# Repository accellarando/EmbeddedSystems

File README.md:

# Embedded Systems Final Project
lightcyan team for University of Utah's ECE 5780 final project.

## Team Members
* Ella Moss
* Ryan Lam
* Matt Alter

## Purpose
The purpose of this project is to create a controllable robot that can navigate an obstacle course without running into any objects.

## Basic Setup

### Hardware
1. Print the chassis linked in the Bill of Materials at 80%, or similar. If using the linked chassis, also print the motor holder.
2. Mount the battery pack behind the motor holders, this will hang over the back edge of the robot.
3. Using a breadboard on the front, mount the two ultrasonic sensors on the left and right sides of the breadboard, and the bluetooth adaptor in the center.
4. Connect the battery pack to one set of power and ground rails, and use a voltage divider to connect the other rail.
5. Wire the components as shown in the Documentation.

### Software
This section assumes that the ARM GNU Toolchain has been [installed](https://developer.arm.com/downloads/-/arm-gnu-toolchain-downloads).
1. `cd Project`
2. Plug in the Discovery board.
3. `make program` to build the project and program the board.

## Usage
To successfully navigate an obstacle course, several UART commands have been implemented -- listed under [Commands](Commands.md).

Users may implement any algorithm for course navigation. Users should use the "Log" command ('l') frequently to check that heading, distance, and ultrasonic data are their expected values.

Values logged are in centimeters for distances and degrees for angles. The rover will automatically stop when an object is 20cm away from an object, at which point the user should turn left or right, then check if the path is clear yet. If two obstacles are next to each other, the user may need to check both left and right before making a decision about how to evade the obstacle. Once the robot is angled toward a path that is clear, continue on that path for a short distance (e.g. 20cm, with the "w1" command). Then, return to 0-degree heading and continue while clear ("w0").

## Bills of Materials
This section provides a list of materials, part numbers, and costs associated with the project.

| Description | Vendor | Part Number | Qty | Total Cost |
|-------------|--------|-------------|-----|------------|
| 3D Printed Chassis | Thingiverse | 1641782| 1 | - |
| 6V Brushed DC Motor | Adafruit | 4638 | 2 | $25.00 |
| Motor Controllers | OSHPark | N/A | 2 | $15.00 |
| Wheel Kit for Motors | Pololu | 1087 | 1 | $3.95 |
| 16mm Caster Wheel | Adafruit | 3949 | 1 | $1.95 |
| STM32F072 Discovery Board | MEB Stockroom | STM32F072B-DISCO | 1 | $12.00 |
| Bluetooth Adapter | ProtoSupplies | HC-05 | 1 | $11.95 |
| Battery Pack | Adafruit | 3859 | 1 | $2.95 |
| Ultrasonic Sensor | Adafruit | 3942 | 3 | $11.85 |
| Voltage Regulator | Wolfwhoop | 5824093032 | 2 | $12.89 |
| | | | **Total:** | **$97.54** |

Additionally, this table lists components required for assembling the motor driver. These component prices vary, but the total tends to be under $10.

| Part     | Manufacturer Short Description | Manufacturer Part # | Qty |
| ----     | ------------------------------ | ------------------- | --- |
| C1       | polarized cap - 1uF            | PREA010M2CBK-0511P  | 1   |
| C2-C4    | ceramic cap - 100nF            | C1206C104K5RAC7800  | 3   |
| R1,R3,R4 | resistor - 10k                 | RC1206JR-0710KLY    | 4   |
| R2       | current sense resistor - 0.04  | RL1206FR-070R04LY   | 1   |
| U5-U8    | diode DO-214AC SMA             | RS2AA R3G           | 4   |
| U1       | dual full bridge motor driver  | L298N               | 1   |
| U2       | digital (I2C) temp sensor      | LM75AIMX/NOPB       | 1   |
| J1-J3, J5| generic pin header             | 68001-121HLF        | 21  |
| J4       | DC power jack                  | CON-SOCJ-2155       | 1   |

## Documentation

## Datasheets 
[6V Brushed DC Motor](https://cdn-shop.adafruit.com/product-files/4638/n20+motors_C15008.pdf)

[Wheel Kit for Motors](https://www.pololu.com/file/0J1708/pololu-wheel-dimensions.pdf)

[16mm Caster Wheel](https://www.adafruit.com/product/3949)

[STM32F0](https://www.st.com/content/ccc/resource/technical/document/datasheet/cd/46/43/83/22/d3/40/c8/DM00090510.pdf/files/DM00090510.pdf/jcr:content/translations/en.DM00090510.pdf)

[STM32F0 Programming Manual](https://www.st.com/content/ccc/resource/technical/document/programming_manual/fc/90/c7/17/a1/44/43/89/DM00051352.pdf/files/DM00051352.pdf/jcr:content/translations/en.DM00051352.pdf)

[STM32F0 Peripheral Manual](https://www.st.com/content/ccc/resource/technical/document/reference_manual/c2/f8/8a/f2/18/e6/43/96/DM00031936.pdf/files/DM00031936.pdf/jcr:content/translations/en.DM00031936.pdf)

[STM32F072RB Discovery Board User Manual](https://www.st.com/content/ccc/resource/technical/document/user_manual/3b/8d/46/57/b7/a9/49/b4/DM00099401.pdf/files/DM00099401.pdf/jcr:content/translations/en.DM00099401.pdf)

[HC-05 Bluetooth Adapter](www.electronicaestudio.com/docs/istd016A.pdf)

[HC-SR04 Ultrasonic Sensor](https://cdn.sparkfun.com/datasheets/Sensors/Proximity/HCSR04.pdf)

### Block diagrams and flow charts
Refer to this simplified block diagram of the rover for an overview, or see the wiring diagram for more details.

### Wiring diagram

### Schematics and PCB layouts
For the custom DC motor driver used in this project, refer to [Motor\_Driver.brd](Motor_Driver.brd) for the PCB layout, and [Motor\_Driver.sch](Motor_Driver.sch) for the circuit schematic. An image of this motor driver schematic is also displayed below for convenience.

## Further areas of research

### Autonomous Control
The original project proposal included some support for autonomous robot control, allowing the robot to navigate the course with minimal human input.

However, due to time constraints and limited testing time, we decided not to implement this feature. The ProcessCommand function will accept a 'p' command to Proceed, but it simply prints out "Not yet implemented." This is the primary area of potential improvement for the project.

The semi-autonomous algorithm was described with this flowchart.

### Force Sensing
The original project proposal also listed force sensors as a secondary sensor we could use. These would act as a failsafe to prevent moving obstacles around, in case of ultrasonic sensor failure.

### Voltage Regulators
The voltage regulators used did not come in a DIP (dual inline package) and were not designed for use in a breadboard. They work fine, but getting the wires to connect with breadboard terminals proved difficult. A chip such as the LM7805 may be more robust, easier to implement, and cheaper.

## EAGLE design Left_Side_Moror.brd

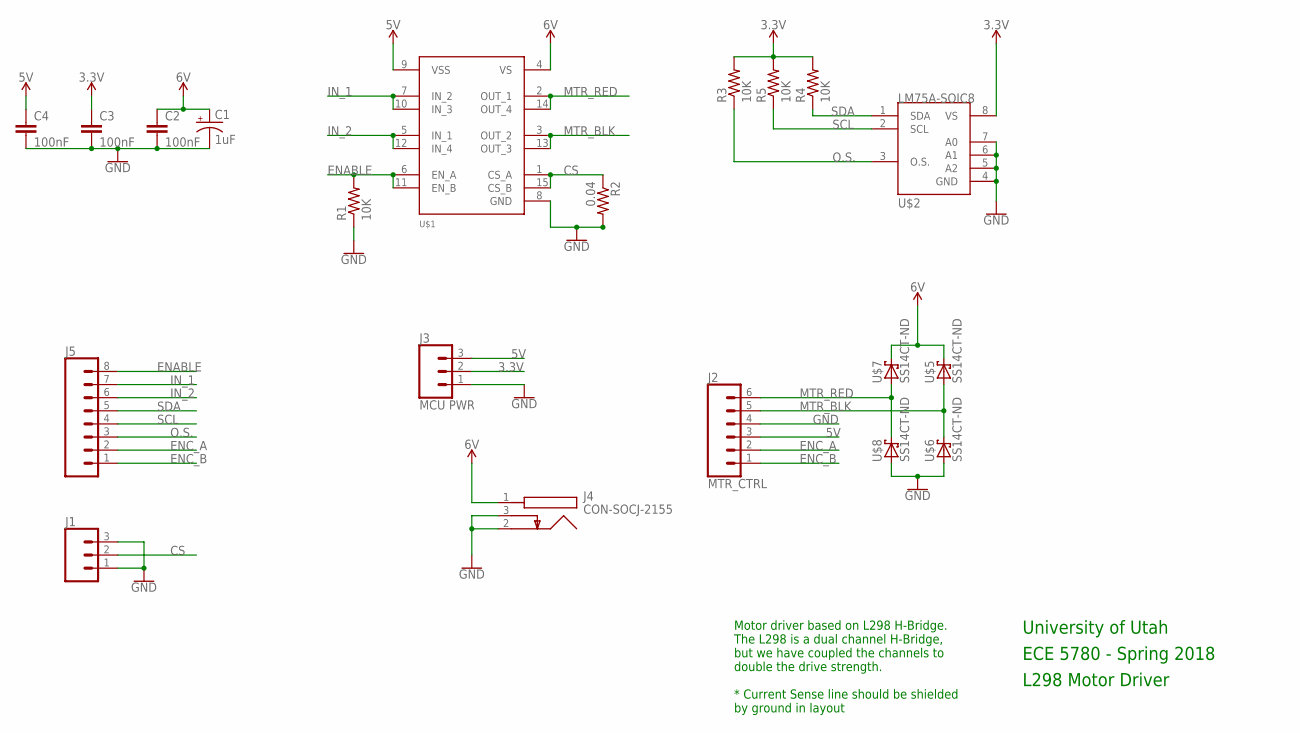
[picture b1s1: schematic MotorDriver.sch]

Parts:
C1: 1uF; E2,5-6
C2, C3, C4: 100nF; C1206
J1: CONN_03; 1X03
J2: MTR_CTRL; 1X06
J3: MCU PWR; 1X03
J4: CON-SOCJ-2155; CONSOCJ2155
J5: CONN_08"; 1X08
R1, R3, R4, R5: 10K; M1206
R2: 0.04; M1206
U$1: L298N-MULTIWATT15
U$2: LM75A-SOIC8; SOIC-8
U$5, U$6, U$7, U$8: SS14CT-ND; SOD106A-W

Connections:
3.3V: C3.1, J3.2, R3.2, R4.2, R5.2, U$2.8 (VS)
5V: C4.1, J2.3, J3.3, U$1.9 (VSS)
CS: J1.2, R2.1, U$1.1 (CS_A), U$1.15 (CS_B)
ENABLE: J5.8, R1.2, U$1.6 (EN_A), U$1.11 (EN_B)
ENC_A: J2.2, J5.2
ENC_B: J2.1, J5.1
GND: C1.-, C2.2, C3.2, C4.2, J1.1, J1.3, J2.4, J3.1, J4.2, J4.3, R1.1, R2.2, U$1.8 (GND), U$2.4 (GND), U$2.5 (A2), U$2.6 (A1), U$2.7 (A0), U$6.A, U$8.A
IN_1: J5.7, U$1.7 (IN_2), U$1.10 (IN_3)
IN_2: J5.6, U$1.5 (IN_1), U$1.12 (IN_4)
MTR_BLK: J2.5, U$1.3 (OUT_2), U$1.13 (OUT_3), U$5.A, U$6.C
MTR_RED: J2.6, U$1.2 (OUT_1), U$1.14 (OUT_4), U$7.A, U$8.C
O.S.: J5.3, R3.1, U$2.3 (O.S.)
SCL: J5.4, R5.1, U$2.2 (SCL)
SDA: J5.5, R4.1, U$2.1 (SDA)
VCC: C1.+, C2.1, J4.1, U$1.4 (VS), U$5.C, U$7.C

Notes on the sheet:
University of Utah
ECE 5780 - Spring 2018
L298 Motor Driver
Motor driver based on L298 H-Bridge. The L298 is a dual channel H-Bridge, but we have coupled the channels to double the drive strength. * Current Sense line should be shielded by ground in layout

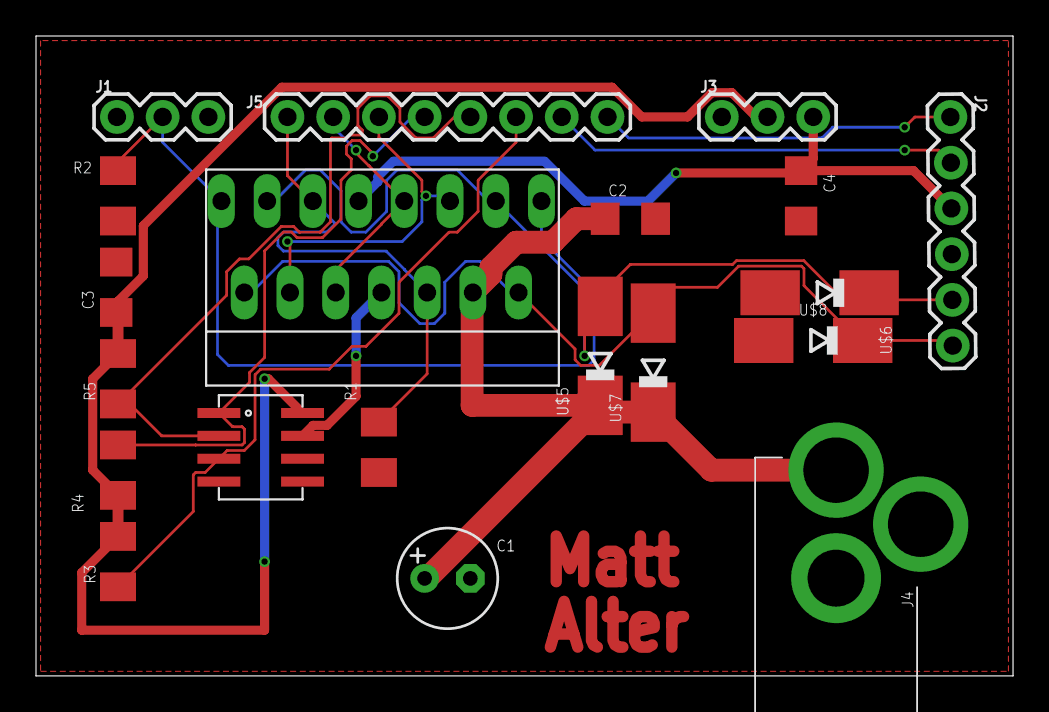
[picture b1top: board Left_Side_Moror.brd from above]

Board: 2 copper layers, 54.3 x 35.6 mm, 20 parts (0 on the bottom side), 15 nets.

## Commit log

2023-03-02 Added my name
2023-03-02 Added name to README
2023-03-17 added commands doc
2023-03-17 fixed md tables
2023-03-17 edits to command descriptions/specifications
2023-03-17 added usart project
2023-04-11 added cad files
2023-04-11 unzipped
2023-04-18 added pinouts
2023-04-18 added pin header/src files
2023-04-19 pins
2023-04-19 commented out extraneous ultrasonic init
2023-04-19 Added Lab7 Motor Files
2023-04-19 makefile
2023-04-19 Added delays between motor toggles
2023-04-19 Updated PB3 to AF2 (TIM2_CH2)
2023-04-19 DRIVES
2023-04-20 uart fixes
2023-04-20 some refactor
2023-04-20 motor refactor
2023-04-20 typo
2023-04-20 stash before merge
2023-04-20 pwm offset for testing
2023-04-22 changed encoder timer channels
2023-04-25 Adds target distance setting and encoder checks
2023-04-25 Adds absolute distance calculation
2023-04-25 not breaking anything i promise
2023-04-25 now it drives for sure for sure
2023-04-25 added a print_debug flag
2023-04-26 Update to use absolute value of right motor speed in ratio calculation
2023-04-26 trying some other ultrasonic sensor stuff
2023-04-26 kinda works
2023-04-26 added notes from meeting
2023-04-28 working!
2023-04-28 wrapping up for the day
2023-04-29 broke everything for a second but now it works again !
2023-04-29 Update main.c
    Updated timeout for ultrasonic sensors so the value no longer overflows
2023-04-29 Update main.c
    Changed the way we send the ultrasonic pulses.
2023-04-30 ultrasonics should be working now
2023-04-30 everything seems to be working well now
2023-04-30 removed some debug prints
2023-05-02 robot ready, angle adjustments, etc
2023-05-02 Partial update of README
2023-05-02 Physical Setup of System
2023-05-02 readme additions
2023-05-02 images etc
2023-05-02 cleaned up, moved main project to Project directory
2023-05-02 reorganize, update pinouts
2023-05-02 Add Wiring Diagram
2023-05-02 more future research in readme
2023-05-02 added software build instructions
2023-05-02 fixed indentation
2023-05-02 added wiring diagram link to readme

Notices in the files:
parts and their libraries:
SparkFun-Connectors: Licensing: Creative Commons ShareAlike 4.0 International - https://creativecommons.org/licenses/by-sa/4.0
